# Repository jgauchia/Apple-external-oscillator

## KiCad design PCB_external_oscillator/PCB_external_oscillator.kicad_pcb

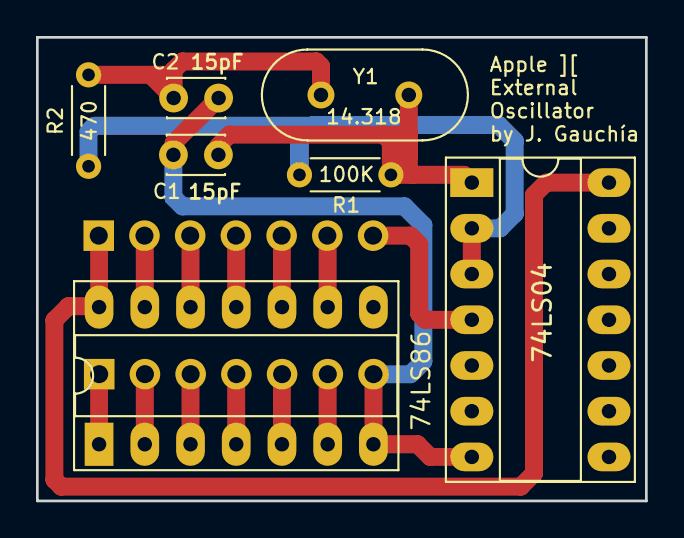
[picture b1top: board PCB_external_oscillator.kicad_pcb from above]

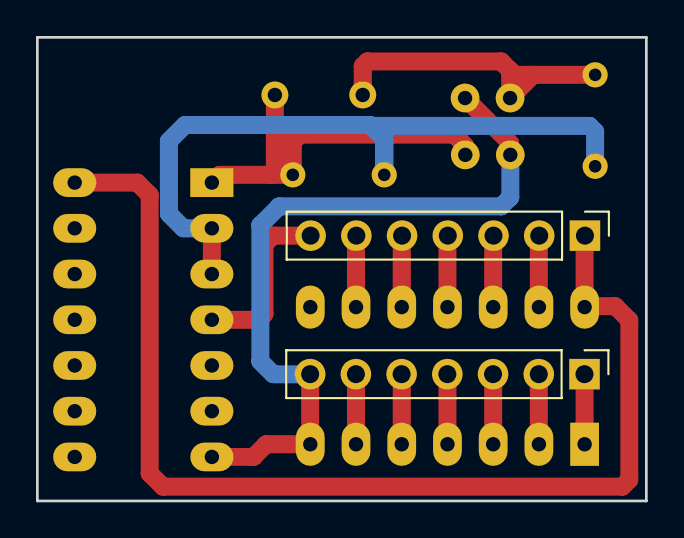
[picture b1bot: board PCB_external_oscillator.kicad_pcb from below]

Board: 2 copper layers, 33.8 x 25.8 mm, 9 parts (2 on the bottom side), 6 nets.

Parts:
74LS86: DIP-14_W7.62mm_Socket_LongPads
C1, C2: 15pF; C_Disc_D3.0mm_W2.0mm_P2.50mm
J1, J2: PinHeader_1x07_P2.54mm_Vertical
R1: 100K; R_Axial_DIN0204_L3.6mm_D1.6mm_P5.08mm_Horizontal
R2: 470; R_Axial_DIN0204_L3.6mm_D1.6mm_P5.08mm_Horizontal
U1: 74LS04; DIP-14_W7.62mm_Socket_LongPads
Y1: 14.318; Crystal_HC49-4H_Vertical

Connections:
+5V: 74LS86.14, J1.1, U1.14 (VCC)
CLK: J1.7, U1.4
GND: 74LS86.7, C1.2, C2.2, J2.7, U1.7 (GND)
unnamed: C1.1, R1.1, U1.1, Y1.1
unnamed: C2.1, R2.2, Y1.2
unnamed: R1.2, R2.1, U1.2, U1.3
